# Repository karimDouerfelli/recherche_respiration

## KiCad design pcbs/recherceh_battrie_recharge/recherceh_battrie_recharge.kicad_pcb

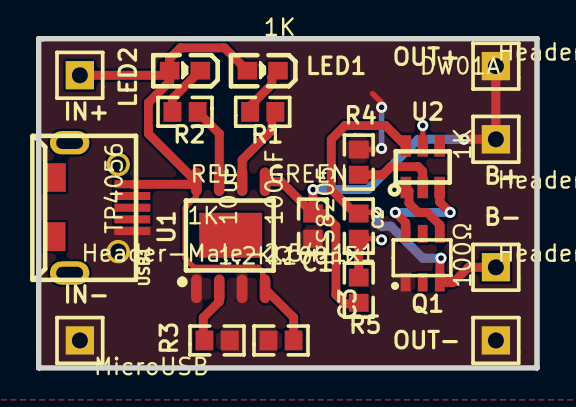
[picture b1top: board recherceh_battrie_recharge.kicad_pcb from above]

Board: 2 copper layers, 27.7 x 18.3 mm, 20 parts (0 on the bottom side), 13 nets.

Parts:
B+: Header-Male-2.54_1x1; HDR-1X1/2.54
B-: Header-Male-2.54_1x1; HDR-1X1/2.54
C1: 10uF; 0603
C2, C3: 100nF; 0603
IN+: Header-Male-2.54_1x1; HDR-1X1/2.54
IN-: Header-Male-2.54_1x1; HDR-1X1/2.54
LED1: GREEN; LED-0603
LED2: RED; LED-0603
OUT+: Header-Male-2.54_1x1; HDR-1X1/2.54
OUT-: Header-Male-2.54_1x1; HDR-1X1/2.54
Q1: FS8205; SOT-23-6
R1, R2, R4: 1K; 0603
R3: 1.2KΩ; 0603
R5: 100Ω; 0603
U1: TP4056; SOP-8_EP_150MIL
U2: DW01A; SOT-23-6L
USB1: MicroUSB; MICRO-USB-1

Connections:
GND: C1.1, C3.1, IN-.1, OUT-.1, Q1.1, R3.2, R4.1, U1.1, U1.3, USB1.5
LED1_2: LED1.2, R1.1
LED2_2: LED2.2, R2.2
Q1_3: B-.1, C2.2, Q1.3, U2.6
Q1_4: Q1.4, U2.1
Q1_6: Q1.6, U2.3
U1_2: R3.1, U1.2
U1_5: B+.1, C1.2, OUT+.1, R5.2, U1.5
U1_6: R1.2, U1.6
U1_7: R2.1, U1.7
U2_2: R4.2, U2.2
U2_5: C2.1, R5.1, U2.5
USB1_1: C3.2, IN+.1, LED1.1, LED2.1, U1.4, U1.8, USB1.1

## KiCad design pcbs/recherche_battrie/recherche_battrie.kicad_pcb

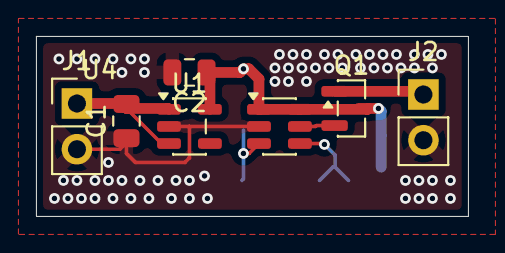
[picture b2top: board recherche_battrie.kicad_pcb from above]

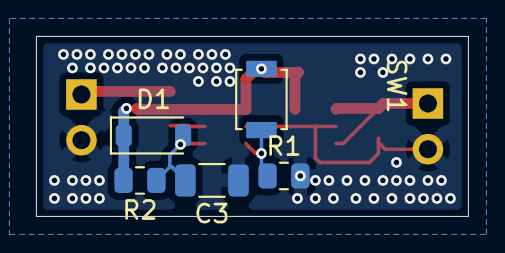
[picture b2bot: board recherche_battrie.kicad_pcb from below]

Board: 2 copper layers, 24.0 x 10.0 mm, 12 parts (5 on the bottom side), 7 nets.

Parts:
C1, C2: 1u; C_0805_2012Metric
C3: 47u; C_1206_3216Metric
D1: D; D_SOD-123
J1, J2: Conn_01x02; PinHeader_1x02_P2.54mm_Vertical
Q1: PMOS; SOT-23
R1: 29.35; R_0805_2012Metric
R2: 1M; R_0805_2012Metric
SW1: SW_Push; SW_SPST_B3U-1000P
U1: LP5907MFX-3.3; SOT-23-5
U4: TPL5110; SOT-23-6

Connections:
+3V3: C2.1, D1.1 (K), Q1.3 (S), R2.2, SW1.2, U1.5 (OUT), U4.1 (VDD), U4.6 (EN/ONE_SHOT)
/bat+: C1.2, J1.1, U1.1 (IN), U1.3 (EN)
GND: C1.1, C2.2, C3.1, J1.2, J2.2, R1.2, U1.2 (GND), U4.2 (GND)
unnamed: C3.2, D1.2 (A), R2.1, U4.4 (DONE)
unnamed: J2.1, Q1.1 (D)
unnamed: Q1.2 (G), U4.5 (DRV)
unnamed: R1.1, SW1.1, U4.3 (DELAY/M_DRV)
